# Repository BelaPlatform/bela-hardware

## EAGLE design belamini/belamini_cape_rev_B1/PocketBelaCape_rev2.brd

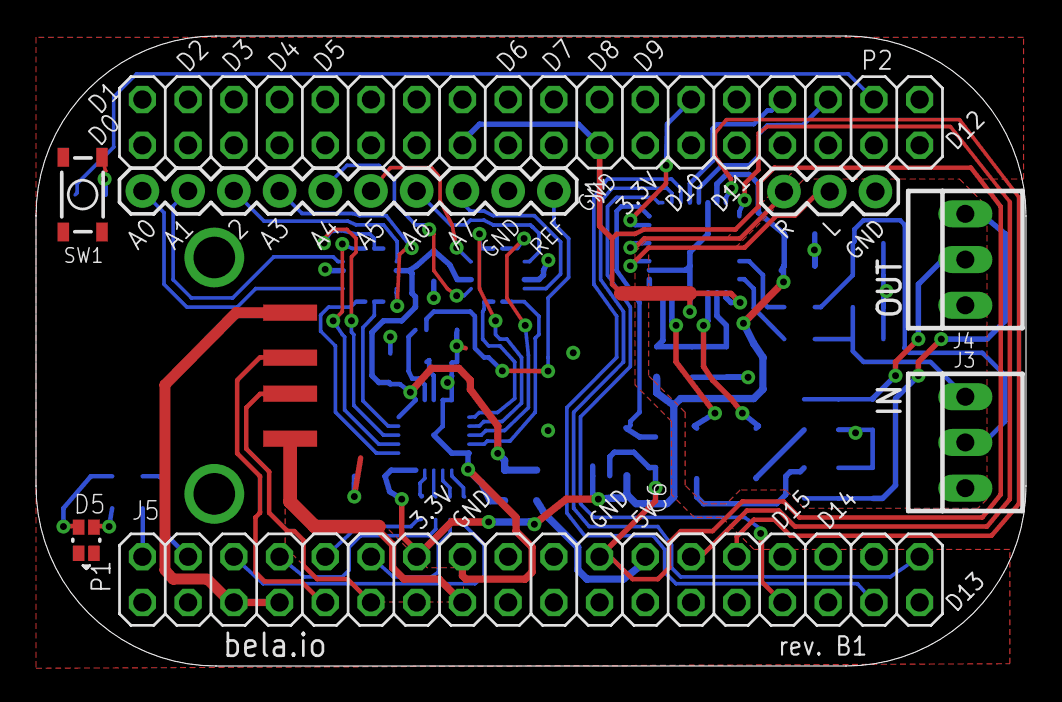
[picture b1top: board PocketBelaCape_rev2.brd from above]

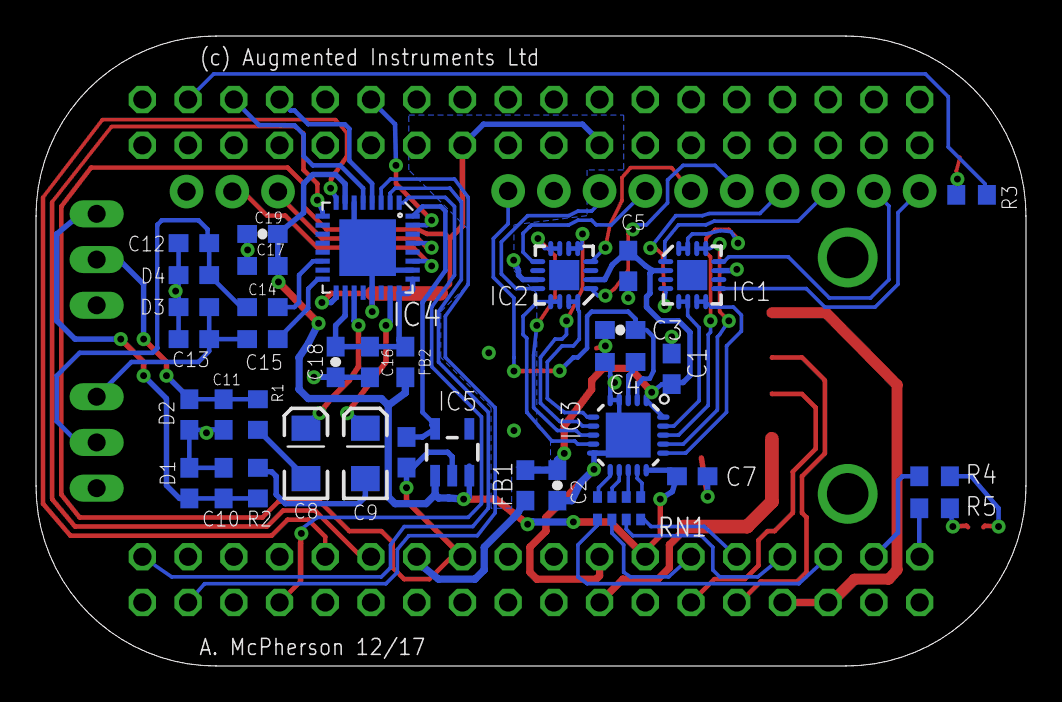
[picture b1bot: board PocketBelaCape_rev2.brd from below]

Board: 2 copper layers, 55.0 x 35.0 mm, 45 parts (36 on the bottom side), 62 nets.

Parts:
C1, C4, C5: 0.1uF; C0603
C2, C3: 10uF; 0603-CAP
C6, C16, C17: 0.1uf; C0603
C7: 1uf; C0603
C8, C9: 47uf; EIA3216
C10, C11, C12, C13: 47pF; C0603
C14, C15: 1uF; C0603
C18, C19: 10uf,10V; 0603-CAP
D1, D2, D3, D4: PGB0010603MR; 0603
D5: LED-RGLTST-C195KGJRKT; LTST-C195KGJRKT
FB1, FB2: FB; 0603
IC1, IC2: ADD8704; QFN16-3X3
IC3: AD7699; LFCSP20-LEADS
IC4: TLV320AIC3104; QFN-32
IC5: V_REG_LDOSMD; SOT23-5
J1: M10SILK_FEMALE_PTH; 1X10
J2: DNI; 1X03
J3, J4: 22-23-2031
J5: USB-A-SMD; USB-A-S-NOSILK-FEMALE
P1, P2: 2X18
R1, R2, R4, R5: 33; R0603
R3: 100; R0603
RN1: 22; 0603-ARC
S1: SWITCH-MOMENTARY-2SMD-5; TACTILE_SWITCH_SMD-4

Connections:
1.8V: C6.1, IC4.32, IC5.5
3.3V: C7.1, C17.1, C19.2, FB2.2, IC3.15, IC4.7, IC5.1, IC5.3, P1.14
+5V_ADC_DAC: C1.1, C2.1, C5.1, FB1.1, IC1.2, IC2.2, IC3.1, IC3.20
+5V_SYS: FB1.2, P1.24
AUDIO_INL: C12.1, C14.1, D4.2, J3.2
AUDIO_INR: C13.2, C15.2, D3.2, J3.3
AUD_3V3: C16.1, C18.2, FB2.1, IC4.18, IC4.24, IC4.25
AUD_BCLK: IC4.2, P1.36
AUD_DIN: IC4.5, P2.32
AUD_DOUT: IC4.4, P2.30
AUD_HPLOUT: C8.A, IC4.19
AUD_HPROUT: C9.A, IC4.23
AUD_MCLK: IC4.1, P1.29
AUD_WCLK: IC4.3, P1.33
GND: C1.2, C2.2, C3.2, C4.2, C5.2, C6.2, C7.2, C10.2, C11.2, C12.2, C13.1, C16.2, C17.2, C18.1, C19.1, D1.1, D2.1, D3.1, D4.1, D5.P$3, D5.P$4, IC1.11, IC2.11, IC3.4, IC3.5, IC3.10, IC3.EXP, IC4.6, IC4.17, IC4.21, IC4.26, IC4.EP, IC5.2, J1.2, J2.1, J3.1, J4.1, P1.16, P1.22, P2.15, P2.21, S1.4
HPL: C11.1, D2.2, J4.2, R1.1
HPR: C10.1, D1.2, J4.3, R2.1
LEFT_LOP: IC4.27, J2.2
LINE1LP: C14.2, IC4.14
LINE1RP: C15.1, IC4.16
unnamed: J5.VBUS, P1.5, P1.7
unnamed: J5.D-, P1.9
unnamed: J5.D+, P1.11
unnamed: IC2.1, J1.6
unnamed: D5.P$2, R4.2
unnamed: IC1.7, IC1.8, IC3.16
unnamed: IC1.13, IC1.14, IC3.17
unnamed: IC2.15, IC2.16, IC3.6
unnamed: IC2.5, IC2.6, IC3.7
unnamed: IC2.7, IC2.8, IC3.8
unnamed: IC2.13, IC2.14, IC3.9
unnamed: D5.P$1, R5.2
unnamed: IC3.11, RN1.4
unnamed: P1.4, R4.1
unnamed: P1.2, R5.1
unnamed: IC3.12, RN1.3
unnamed: C4.1, IC3.3
unnamed: IC3.13, RN1.2
unnamed: IC3.14, RN1.1
unnamed: IC1.5, IC1.6, IC3.19
unnamed: IC1.15, IC1.16, IC3.18
unnamed: IC1.9, J1.10
unnamed: IC1.12, J1.9
unnamed: IC1.1, J1.8
unnamed: IC1.4, J1.7
unnamed: IC2.4, J1.5
unnamed: IC2.9, J1.4
unnamed: IC2.12, J1.3
unnamed: C8.C, R1.2
unnamed: R3.1, S1.1
unnamed: C9.C, R2.2
RESETN: IC4.31, P2.26
RIGHT_LOP: IC4.29, J2.3
SCL: IC4.8, P1.28
SDA: IC4.9, P1.26
SHUTDOWN_REQ/: P2.34, R3.2
SPI_ADC_CNV: P1.6, RN1.5
SPI_MISO: P1.10, RN1.8
SPI_MOSI: P1.12, RN1.6
SPI_SCK: P1.8, RN1.7
USBGND: J5.GND, P1.15
VREF: C3.1, IC3.2, J1.1

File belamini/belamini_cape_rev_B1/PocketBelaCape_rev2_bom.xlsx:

Name | Quantity | Value | Side | Package | Description | Farnell # | Mouser # | Datasheet / Notes
 |  |  |  |  |  |  | 810-C1608X5R1A106M
C2, C3, C18, C19 | 4 | 10uF | bottom | “0603” | Capacitor ceramic 0603 | 2309028
C7, C14, C15 | 3 | 1uF | bottom | “0603” | Capacitor ceramic 0603 | 2496916 | 77-VJ0603V105MXQPBC
C1, C4, C5, C6, C16, C17 | 6 | 0.1uF | bottom | “0603” | Capacitor ceramic 0603 | 1709957 | 80-C0603C104K5R
C10, C11, C12, C13 | 4 | 47pF | bottom | "0603" | Capacitor ceramic 0603 | 1759062 | 77-VJ0603A470JXACBC
C8, C9 | 2 | 47uF | bottom | "1206" | Capacitor electrolytic 1206 | 2353044 | 647-F930J476MAA
D1, D2, D3, D4 | 4 | TE Connectivity PESD0603-240 | bottom | "0603" | ESD suppressor 24V |  | 650-PESD0603-240
D5 | 1 | Lite-On LTST-C195TBJRKT | top | “0606” | blue/red LED |  | 859-LTST-C195TBJRKT
FB1, FB2 | 4 | Ferrite bead | bottom | “0603” | Ferrite bead 0603 | 1781090 | 810-MPZ1608S121A
IC1, IC2 | 2 | TSV524 | bottom | QFN-16 | Quad op-amp |  | 511-TSV524IQ4T
IC3 | 1 | AD7699 | bottom | LFCSP-20 | 16-bit ADC |  | 584-AD7699BCPZ
IC4 | 1 | TLV320AIC3104 | bottom | QFN-32 | Audio codec |  | 595-TLV320C3104IRHBR
IC5 | 1 | MIC5317 | bottom | SOT23-5 | 1.8V regulator |  | 998-MIC5317-1.8YM5TR
J1 | 1 | 10-pin socket | top | Through Hole | 10-pin socket |  | 992-10FX1-254MM
J2 | 1 | 3-pin header | top | Through Hole | 3-pin socket |  | 855-M20-7820346
J3, J4 | 2 | Molex 3-pin | top | Through Hole | 3-pin Molex KK series connector |  | 538-22-23-2031
J5 | 1 | Amphenol 87583-3010RPALF | top | Solder Pad | USB A socket, solder pad | 1314363 | 649-87583-3010RPALF
P1, P2 | 2 | 36-pin header | top | Through Hole | 2x18 2.54mm stacking headers (long male pins on bottom, female sockets on top) |  |  | similar to headers used on bela_cape but 36 pins rather than 46 pins
R1, R2 | 2 | 33 ohm | bottom | “0603” | Resistor 0603
R3 | 1 | 100 ohm | bottom | “0603” | Resistor 0603
R4, R5 | 2 | 560 ohm | bottom | “0603” | Resistor 0603
RN1 | 1 | 22 ohm 4x network | bottom | “0603” | Resistor network 4x0603 | 2060086
S1 | 1 | C&K Components PTS810 SJG 250 SMTR LFS | top | SMD | Micro tactile switch |  | 611-PTS810SJG250SMTR
Total | 47
BOM rev. B1

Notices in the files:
parts and their libraries:
SparkFun-Capacitors: Licensing: CC v3.0 Share-Alike You are welcome to use this library for commercial purposes.
SparkFun-LED: Licensing: Creative Commons ShareAlike 4.0 International - https://creativecommons.org/licenses/by-sa/4.0
